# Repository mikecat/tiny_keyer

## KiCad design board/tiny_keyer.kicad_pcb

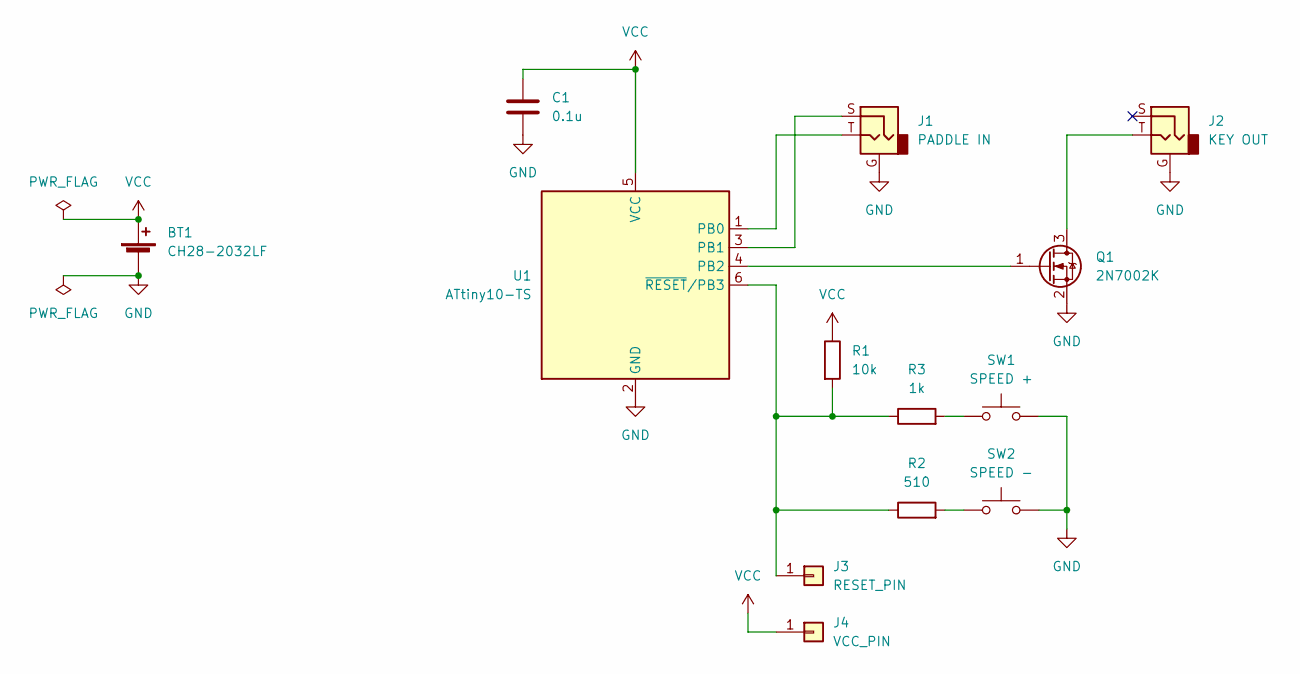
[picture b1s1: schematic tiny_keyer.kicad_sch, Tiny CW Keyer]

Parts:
BT1: CH28-2032LF
C1: 0.1u; C_0805_2012Metric_Pad1.18x1.45mm_HandSolder
J1: PADDLE IN; Jack_3.5mm_Switronic_ST-005-G_horizontal
J2: KEY OUT; Jack_3.5mm_Switronic_ST-005-G_horizontal
J3: RESET_PIN; PinHeader_1x01_P2.54mm_Vertical
J4: VCC_PIN; PinHeader_1x01_P2.54mm_Vertical
Q1: 2N7002K; SOT-23_Handsoldering
R1: 10k; R_0805_2012Metric_Pad1.20x1.40mm_HandSolder
R2: 510; R_0805_2012Metric_Pad1.20x1.40mm_HandSolder
R3: 1k; R_0805_2012Metric_Pad1.20x1.40mm_HandSolder
SW1: SPEED +; TVAF06-A020B-R
SW2: SPEED -; TVAF06-A020B-R
U1: ATtiny10-TS; SOT-23-6

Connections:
GND: BT1.2 (-), C1.2, J1.G, J2.G, Q1.2 (S), SW1.2, SW2.2, U1.2 (GND)
unnamed: J2.T, Q1.3 (D)
unnamed: R2.2, SW2.1
unnamed: R3.2, SW1.1
unnamed: J1.T, U1.1 (PB0)
unnamed: J1.S, U1.3 (PB1)
unnamed: Q1.1 (G), U1.4 (PB2)
unnamed: J3.1, R1.2, R2.1, R3.1, U1.6 (~RESET/PB3)
VCC: BT1.1 (+), C1.1, J4.1, R1.1, U1.5 (VCC)

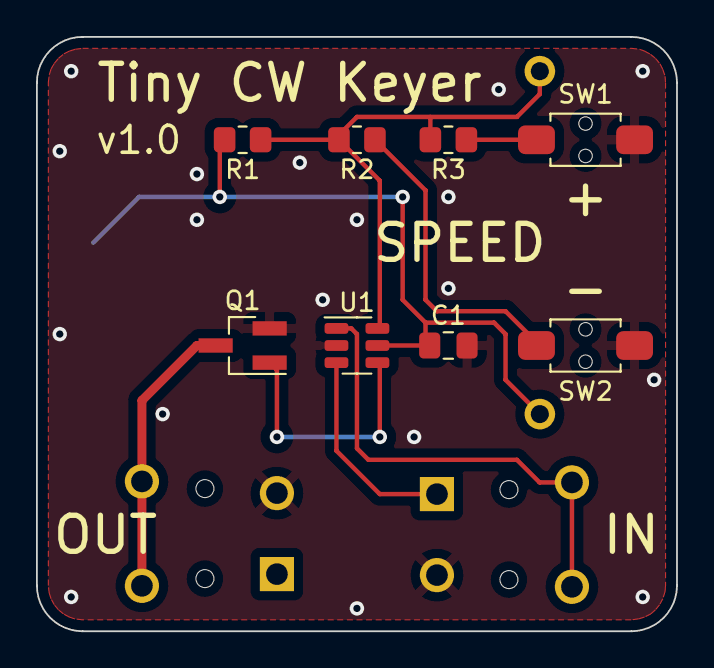
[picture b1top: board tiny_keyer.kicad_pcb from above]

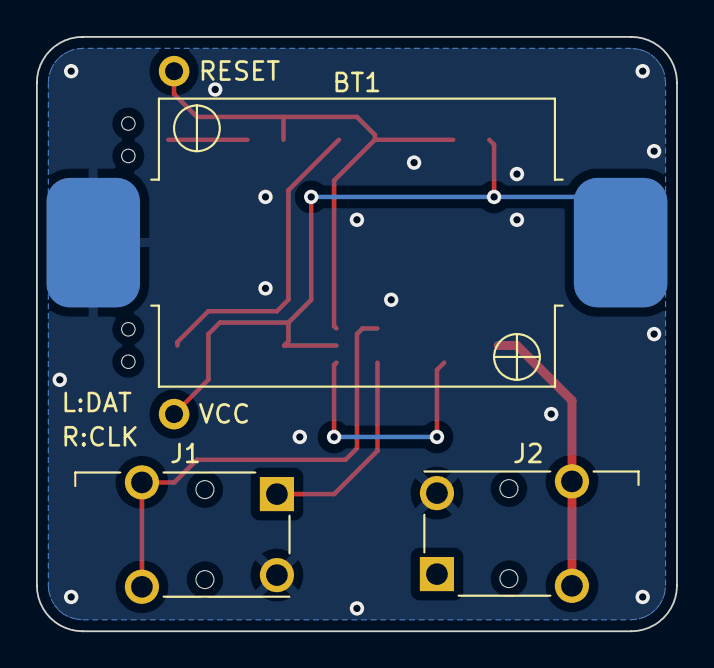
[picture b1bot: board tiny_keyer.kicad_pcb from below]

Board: 2 copper layers, 35.6 x 33.0 mm, 13 parts (3 on the bottom side), 9 nets.

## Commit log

2023-01-15 first commit: add board design
2023-01-27 remove and ignore backups
2023-01-27 output gerver files
